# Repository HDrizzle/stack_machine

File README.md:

# Stack Machine Version 2

</img>

Photo of Version 1

## Changes from previous version

* The timing will be completely redone: A single normal clock signal, not the stupid "AB Alternating" I made up for the original.
* The PC will be incremented and a new instruction fetched during any non-flow-control instructions except when the GPRAM is used and the PC is in the same RAM chip (the RAM chips have 15 address lines each) as whatever is being accessed. The bus timing will also be very flexible and will be faster when possible but still slow when the memory is being accessed twice for example.
* Bus read/write addresses are both now 5 bits. The WRITE/MOVE instruction formats will remain the same and the extra bit (MSB to be exact) will be set based on duplicate opcodes for WRITE/MOVE that are otherwise interpreted the same. 1 extra WRITE opcode and 3 extra MOVE opcodes.
* The opcode decoder is actually 3 bits. There will be 4 bits used for extra MOVE/WRITE instructions (see above).
* Interrupts: There will be seperate interrupt GOTO latches that go to a dedicated interrupt handler function. That function should save the state of everything else (including the regular GOTO latches, which is why interrupt GOTO latches are seperate) onto the stack then do whatever depending on the interrupt code.
* GOTO latches can be written to the bus (see above). The goto decider doesn't need to be because it's simple to get its value from an IF-ELSE.
* The control unit will be able to fetch instructions from the GPRAM: Program addresses starting at 2^15 (32,768, halfway through the old flash memory space) will load 2 consecutive bytes (an instruction is 2 bytes) from the GPRAM. The GPRAM address of the first byte (lower byte of the instruction) will be determined by: `(prog_addr - 32,768) * 2`. Since that will only happen at or above 32,768 then the MSB will not be used in the math and will be used to determine whether to read from flash or GPRAM.
* Flash program space is selectable: The flash chips have 17 address lines, while 15 are used (see above about half the program address space being mapped to the GPRAM). This means that the top 2 lines can be connected to jumpers to select between 4 different programs.
* Flash program can be written to from the bus: The programming interface takes 8 data inputs + power and GND. The old interface to plug an Aduino in to program it will still be there of course but it can be selected by a jumper to be either the external pins (to Arduino) or from the bus.
* The stack is 32k instead of 64k so only one memory chip is used, although 32k is still incredibly excessive.

### GPRAM Parallelization

The RAM chips have 15 address lines each so there will be two of them (Lower and Upper Domains). This means that they can be used seperately at the same time, for example fetching the new instruction (If the PC is in the RAM) and also doing GPRAM read/write, as long as these operations are using seperate domains.
Memory users will use either (or both) of the lower or upper RAM domains:

* Program: PC and data read into instruction registers A & B
* Heap R/W: Exactly the same as the original

# Program instructions

Each instruction will be 16 bits and interpreted by the control unit. The first 3 bits (0 - 3) of the instruction will address the below list of operations. The rest of the instruction (bits 4 - 15) may be ignored or used for different things depending on the specific operation.

Here's the current list of the operation codes (opcodes):

0. `MOVE` - Bus usage - The rest of the instruction will be interpreted as follows: bits 8 - 11 address the device which will set the state of the bus (TX) and bits 12 - 15 will address the device to read from it (RX). Bits 4 - 7 are sent to the ALU as it's opcode incase the data is comming from it.
1. `WRITE` - Writes instruction bits 4 - 11 to the bus. Bits 12 - 15 address the device to read from it.
2. `GOTO` - Saves the 2 execution pointer GOTO latches (each of them are 1 byte) to the program counter
3. `GOTO-IF` - Reads the LSB of the value in the goto decider latch and does a GOTO only if it is 1, otherwise does nothing
4. `HALT` - Stops the clock, usefull for debugging
5. `CALL` - Effectively the same as `GOTO` but also pushes the return address (current value of program counter) onto the call stack. Note: The return address can be copied as-is and does not need to be incremented because it will be incremented normally after each `RETURN` instruction when it is used. If bit 4 is 1 this means that this call is calling the interrupt handler using the Interrupt GOTO latches.
6. `RETURN` - The program counter will be set to the return address popped off the top of the call stack. If bit 4 is 1 this means that this return instruction is returning from the interrupt handler function and will allow interrupts again.
7. `CONFIG-INT` - Configure interrupt. Bit 4 enables or disables interrupts. Interrupts are disabled on startup.

The following are treated as either MOVE or WRITE by the sequencer and set the bus TX and RX MSBs. The original MOVE and WRITE have all MSBs = 0.

8. `MOVE` - MSBs TX=1, RX=0
9. `MOVE` - MSBs TX=0, RX=1
10. `MOVE` - MSBs TX=1, RX=1
11. `WRITE` - MSBs RX=1

# Bus

Up to 15 devices can read the bus and 16 write to it.
Devices that can read the bus (RX):

0. `NONE` - Nothing reads this so that bytes can be popped from the stack without them going anywhere.
1. `STACK-PUSH` - Stack controller (Push)
2. `ALU-A` - ALU latch A
3. `ALU-B` - ALU latch B
4. `GOTO-A` - Control unit - Program counter GOTO latch A (first byte)
5. `GOTO-B` - Control unit - Program counter GOTO latch B (second byte)
6. `GOTO-DECIDER` - Control unit - GOTO decider latch (For GOTO-IF)
7. `GPRAM` - GPRAM - Write
8. `GPRAM-INC-ADDR` - GPRAM - Write (++ address)
9. `GPRAM-ADDR-A` - GPRAM - Address bits 0 - 7
10. `GPRAM-ADDR-B` - GPRAM - Address bits 8 - 15
11. `GPIO-WRITE-A` - Writes to GPIO output pins 0 - 7
12. `OFFSET-WRITE` - Replaces value in stack at `ToS - offset`
13. `SET-STACK-OFFSET` - Sets the stack offset byte
14. `ALU-C-IN` - ALU latch for carry and borrow, only LSB is used. Make sure this is always zero when not being used otherwise additions will be wrong.
15. `GPIO-WRITE-B` - Writes to GPIO output pins 8 - 15
16. `INT-GOTO-A` - Interrupt GOTO A
17. `INT-GOTO-B` - Interrupt GOTO B
18. `VECTORS-A` - Vector graphics A input
19. `VECTORS-B` - Vector graphics B input
20. `VECTORS-C` - Vector graphics C input
21. `VECTORS-D` - Vector graphics D input
22. `INT-AND-MAIN-TIMER-ADDRESS` - Bits 0 - 1 address 1 of the 4 interrupt timers. Bit 2 will reset the addressed counter to 0.
23. `INT-TIMER-CONFIG-MAX` - Sets the start value of one of the interrupt timers
24. `INT-TIMER-CONFIG-TIMEBASE-AND-ENABLE` - Configures one of the interrupt timers, see `timer_board.md`
25. `FLASH` - Flash programming interface, same as the arduino connection
26. `RX-26` - Expansion RX 25

...

31. `RX-31` - Expansion RX 31

Devices that can write to the bus (TX):

0. `STACK-POP` - Stack controller (pop)
1. `OFFSET-READ` - Reads value from stack at `ToS - offset`, does not affect the ToS
2. `ALU` - ALU output
3. Control unit instruction bits 4 - 11, used for the `WRITE` instruction
4. `GPRAM` - GPRAM - Read
5. `GPRAM-INC-ADDR` - GPRAM - Read (++ address)
6. `GPRAM-ADDR-A` - GPRAM - Address bits 0 - 7
7. `GPRAM-ADDR-B` - GPRAM - Address bits 8 - 15
8. `GPIO-READ-A` - Reads GPIO input pins 0 - 7
9. `MAIN-TIMER` - 8 bits of the main timer, addressed by `INT-AND-MAIN-TIMER-ADDRESS`
10. `INT-TIMER` - Current value of 1 of the 4 interrupt timers, addressed by `INT-AND-MAIN-TIMER-ADDRESS`
11. `GPIO-READ-B` - Reads GPIO input pins 8 - 15
12. `INT-CODE` - Most recent interrupt code, will be cleared upon read
13. `INT-COUNT` - Number of interrupts in queue, will overflow past 255
14. `GET-STACK-OFFSET` - Retrieves stack offset, needed to save state during interrupt
15. `GET-GOTO-A` - Read GOTO Latch A
16. `GET-GOTO-B` - Read GOTO Latch B
17. `TX-17` - Expansion TX 17

...

31. `TX-31` - Expansion TX 31

# The Stack

The stack will simply be a piece of memory seperate from the pGPRAM and managed by hardware, its has 32k x 8-bit words.

There will be two ways to access the stack:

1. Push and Pop
2. Using the current ToS pointer - stack offset (`OFFSET-WRITE` and `OFFSET-READ`) (does not change ToS). The stack offset will be a 1-byte number set from the bus (`SET-STACK-OFFSET`) and will not affect pushes and pops.

# ALU

The ALU uses 2 8-bit latches for input and has 1 output. The specific operation it does is controlled by 4 bits (2^4 = 16 operations). All operations that result in a boolean output all `0`s except for the result which is the LSB.

0. `ADD` - Add
1. `ADD-C` - Addition carry output (just the LSB will be set), this can be written directly into `ALU-C-IN`
2. `NOT` - Bitwise NOT (latch A)
3. `OR` - Bitwise OR
4. `AND` - Bitwise AND
5. `XNOR` - Bitwise XNOR, whether each pair of bits are equal
6. `SHIFT` - Bitshifts A left by the first 3 bits of B, bits that go off the end DO wrap around.
7. `EQ` - Whether bytes are equal
8. `A` - Contents of A latch
9. `B` - Contents of B latch
10. `EXT-10` - Extension (not implemented)
11. `EXT-11` - Extension (not implemented)
12. `EXT-12` - Extension (not implemented)
13. `EXT-13` - Extension (not implemented)
14. `EXT-14` - Extension (not implemented)
15. `EXT-15` - Extension (not implemented)

# Flow Control

There are four instructions for flow control: `GOTO`, `GOTO-IF`, `CALL`, and `RETURN`.

## GOTO and GOTO-IF

A `GOTO` instruction is used to jump to anywhere in the program. it uses the two 8-bit latches (`GOTO-A` and `GOTO-B`) to set the 16-bit program counter. Due to how the hardware is set up, the PC will be incremented after each goto instruction. This means that the previous address to where the execution should jump to must be used.

`GOTO-IF` is a conditional goto which will do what is described above only if the bit set by `GOTO-DECIDER` from the LSB of the bus is 1, otherwise it does nothing. This is the only instruction that allows the computer to "branch" or "make decisions".

There are macros, `@goto(anchor_name)` and `@goto_if(anchor_name)` that make GOTOs a lot easier.

## Functions and the call stack

Functions in the machine code are defined by `CALL` and `RETURN` instructions. To call a function, make sure the correct pointer to the beginning of the function is stored in the control unit goto A and B latches. Then use the `CALL` instruction which is basically a GOTO but will first put the current program counter value onto the call stack as the return address. The return instruction pops a return address off of the call stack and continues execution.

There is a macro in the assembly language, `@call(function_name)` that makes calling a lot easier.

The call stack is a seperate stack memory containing 256 (1 byte address size) 16-bit words. Each word will be a return address - where to set the program counter during a `RETURN` instruction.

# I/O

There are 16 input and 16 seperate output pins accessible with the `GPIO-READ-A`, `-B` and `GPIO-WRITE-A`, `-B` bus sources/destinations.

## Writing to the display

The display has 32 x 32 LEDs, any given row of 8 pixels are written all at once with one byte. These rows of 8 are addressed by a 7-bit number starting at the top-left and going across for 4 per row (32 / 8 = 4) for each of the 32 rows of the display. The display currently is attached to the gpio-write a and b outputs with gpio-write-a being the address (MSB is ignored) and gpio-write-b being the data. The signal to write the address/data to the display's memory is sent by the hardware when gpio-write-b is written to, meaning the address should be written first and then the data.

# General purpose static-RAM (GPRAM)

This piece of memory does not have any hardware protection like the stack and can be writen to and read from at any location. It will have a 16-bit address by 8-bit word size (65,536 bytes) just like the stack.

Its address can be optionally incremented upon reads/writes and can be directly set from the bus (`GPRAM-ADDR-A` and `GPRAM-ADDR-B`). For the instructions where the address is incremented, that will happen after the read/write.

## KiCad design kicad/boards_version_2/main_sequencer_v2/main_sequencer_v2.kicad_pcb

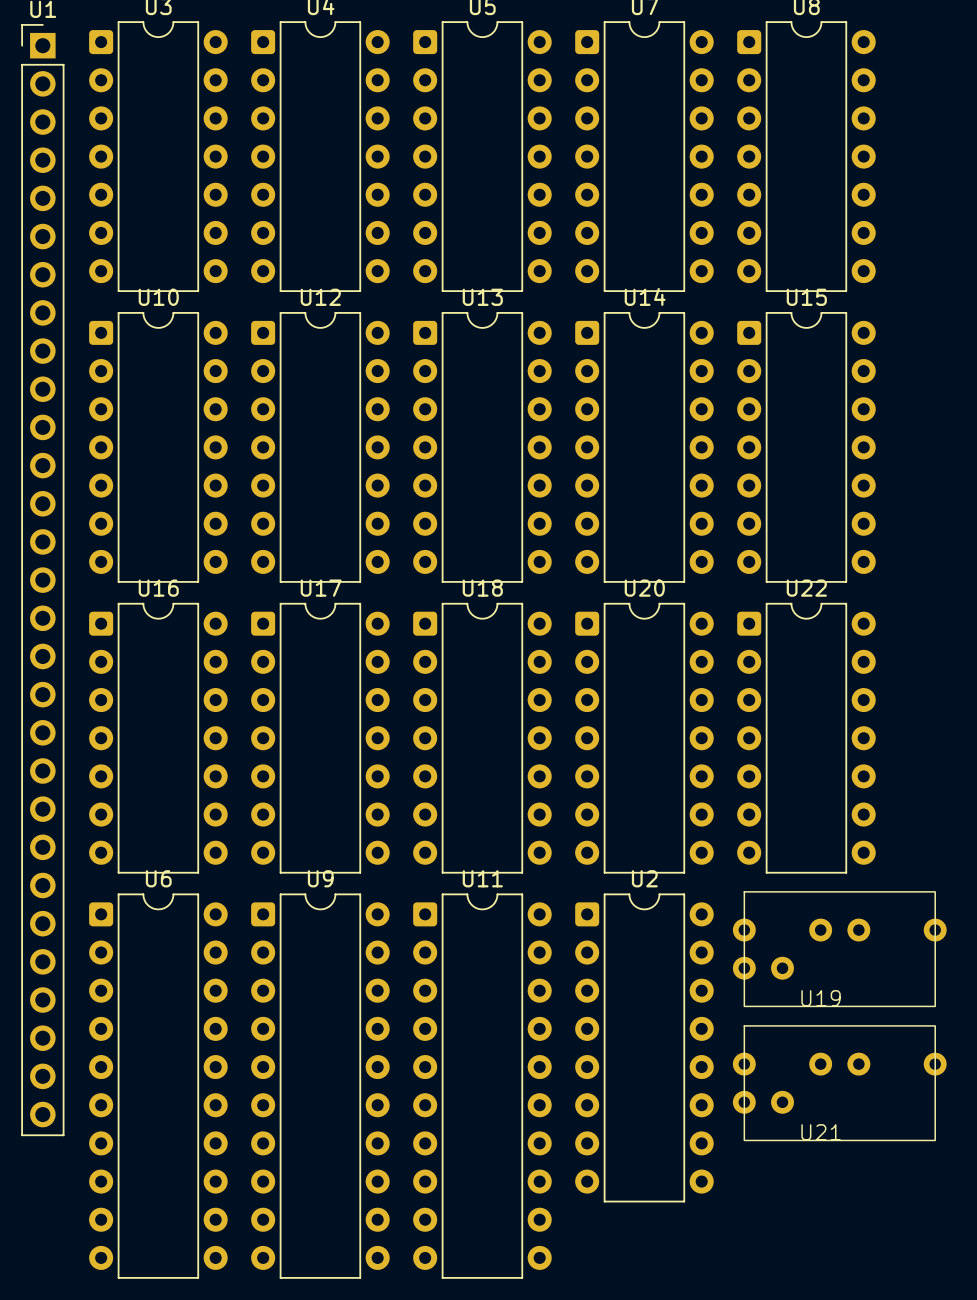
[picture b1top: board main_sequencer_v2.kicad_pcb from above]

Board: 2 copper layers, 22 parts (0 on the bottom side), 80 nets, no tracks yet.

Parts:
U1: PinHeader_1x29_P2.54mm_Vertical
U2: DIP-16_W7.62mm
U3, U4, U5, U7, U8, U10, U12, U13, U14, U15, U16, U17, U18, U20, U22: DIP-14_W7.62mm
U6, U9, U11: DIP-20_W7.62mm
U19, U21: jumper

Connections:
unnamed: U1.13 (Bus_move), U8.4 (Q1), U8.13 (3B)
unnamed: U1.2 (Bus_move_done), U16.4 (A2)
unnamed: U1.4 (CLK), U3.1 (I0), U9.11 (CLK)
unnamed: U1.5 (Enable), U4.1 (1A), U18.13 (I5)
unnamed: U1.3 (GOTO_Decider), U10.1 (0A)
unnamed: U1.16 (GOTO_latches_OE), U15.3 (1Q)
unnamed: U1.15 (INT-GOTO_latches_OE), U15.6 (2Q)
unnamed: U1.21 (Instruction++), U3.12 (O5)
unnamed: U1.9 (Instruction_bit_4), U3.5 (I2), U7.5 (0D), U13.2 (1B), U13.4 (2A), U13.10 (4A)
unnamed: U1.6 (Opcode_(3-bit)_0), U2.1 (A0)
unnamed: U1.7 (Opcode_(3-bit)_1), U2.2 (A1)
unnamed: U1.8 (Opcode_(3-bit)_2), U2.3 (A2)
unnamed: U1.17 (Post-adder_latch_OE), U5.4 (Q1)
unnamed: U1.19 (Pre-adder_latch_CLK), U9.4 (D2), U17.1 (OA)
unnamed: U1.11 (Start_-edge), U10.9 (2B)
unnamed: U2.6 (E1), U4.3 (1Q), U4.13 (3A)
unnamed: U2.4 (E2#), U2.5 (E3#), U2.8 (GND)
unnamed: U2.15 (Y0), U8.5 (1A)
unnamed: U2.14 (Y1), U8.6 (1B)
unnamed: U2.12 (Y3), U8.9 (2B)
unnamed: U2.11 (Y4), U6.5 (D3), U8.1 (0A)
unnamed: U2.10 (Y5), U6.2 (D0)
unnamed: U2.9 (Y6), U6.9 (D7)
unnamed: U3.4 (O1), U4.12 (3B)
unnamed: U4.11 (3Q), U6.8 (D6)
unnamed: U5.1 (0A), U9.17 (Q2)
unnamed: U6.18 (Q1), U9.3 (D1)
unnamed: U7.4 (0RESET), U7.6 (0SET), U7.7 (GND)
unnamed: U8.3 (Q0), U8.12 (3A)
unnamed: U2.13 (Y2), U8.8 (2A), U10.2 (0B)
unnamed: U6.3 (D1), U9.19 (Q0), U10.5 (1A)
unnamed: U6.19 (Q0), U7.3 (0CLK), U9.2 (D0), U10.6 (1B), U13.1 (1A)
unnamed: U6.15 (Q4), U10.8 (2A)
unnamed: U6.4 (D2), U9.18 (Q1), U10.12 (3A), U14.13 (3A)
unnamed: U10.13 (3B), U14.6 (2Q)
unnamed: U3.11 (I4), U10.3 (Q0), U14.4 (2A)
unnamed: U10.4 (Q1), U16.10 (B1)
unnamed: U10.10 (Q2), U17.3 (A1)
unnamed: U10.11 (Q3), U15.2 (1B), U15.5 (2B)
unnamed: U3.14 (V+), U8.14 (V+), U10.14 (V+), U13.14 (V+), U16.14 (V+)
unnamed: U3.2 (O0), U6.11 (CLK), U11.11 (CLK)
unnamed: U2.7 (Y7), U8.2 (0B), U11.2 (D0)
unnamed: U6.1 (OE#), U6.10 (GND), U9.1 (OE#), U9.10 (GND), U11.10 (GND)
unnamed: U11.19 (Q0), U13.9 (4B), U13.12 (3B), U16.5 (A3)
unnamed: U6.20 (V+), U9.20 (V+), U11.20 (V+)
unnamed: U12.1 (0A), U18.6 (O2), U19.1 (IN)
unnamed: U12.2 (0B), U13.3 (1Q)
unnamed: U12.5 (1A), U18.4 (O1)
unnamed: U5.10 (Q2), U12.6 (1B)
unnamed: U12.8 (2A), U18.10 (O4), U21.1 (IN)
unnamed: U12.9 (2B), U13.8 (4Q)
unnamed: U12.12 (3A), U18.8 (03)
unnamed: U5.11 (Q3), U12.13 (3B)
unnamed: U12.3 (Q0), U18.3 (I1)
unnamed: U12.4 (Q1), U18.5 (I2)
unnamed: U12.10 (Q2), U18.9 (I3)
unnamed: U12.11 (Q3), U18.11 (I4)
unnamed: U3.13 (I5), U5.8 (2A), U13.6 (2Q)
unnamed: U3.6 (O2), U13.13 (3A)
unnamed: U5.13 (3B), U13.11 (3Q)
unnamed: U3.10 (O4), U14.1 (1A)
unnamed: U6.6 (D4), U8.10 (Q2), U14.2 (1B), U14.5 (2B)
unnamed: U14.3 (1Q), U16.9 (B0)
unnamed: U7.1 (0Q), U14.12 (3B)
unnamed: U3.9 (I3), U14.11 (3Q), U15.4 (2A)
unnamed: U14.9 (4B), U21.3 (OUT)
unnamed: U3.8 (03), U15.1 (1A)
unnamed: U15.13 (3A), U16.1 (OA), U18.1 (I0)
unnamed: U15.12 (3B), U18.2 (O0)
unnamed: U6.13 (Q6), U16.2 (A0)
unnamed: U6.16 (Q3), U16.3 (A1)
unnamed: U3.3 (I1), U6.7 (D5), U8.11 (Q3), U16.11 (B2)
unnamed: U5.3 (Q0), U16.12 (B3)
unnamed: U5.5 (1A), U16.13 (OB)
unnamed: U6.14 (Q5), U17.2 (A0)
unnamed: U6.17 (Q2), U17.4 (A2)
unnamed: U6.12 (Q7), U17.5 (A3)
unnamed: U17.7 (GND), U17.12 (B3)
unnamed: U5.9 (2B), U5.12 (3A), U18.12 (O5)
unnamed: U19.2 (GND), U21.2 (GND)

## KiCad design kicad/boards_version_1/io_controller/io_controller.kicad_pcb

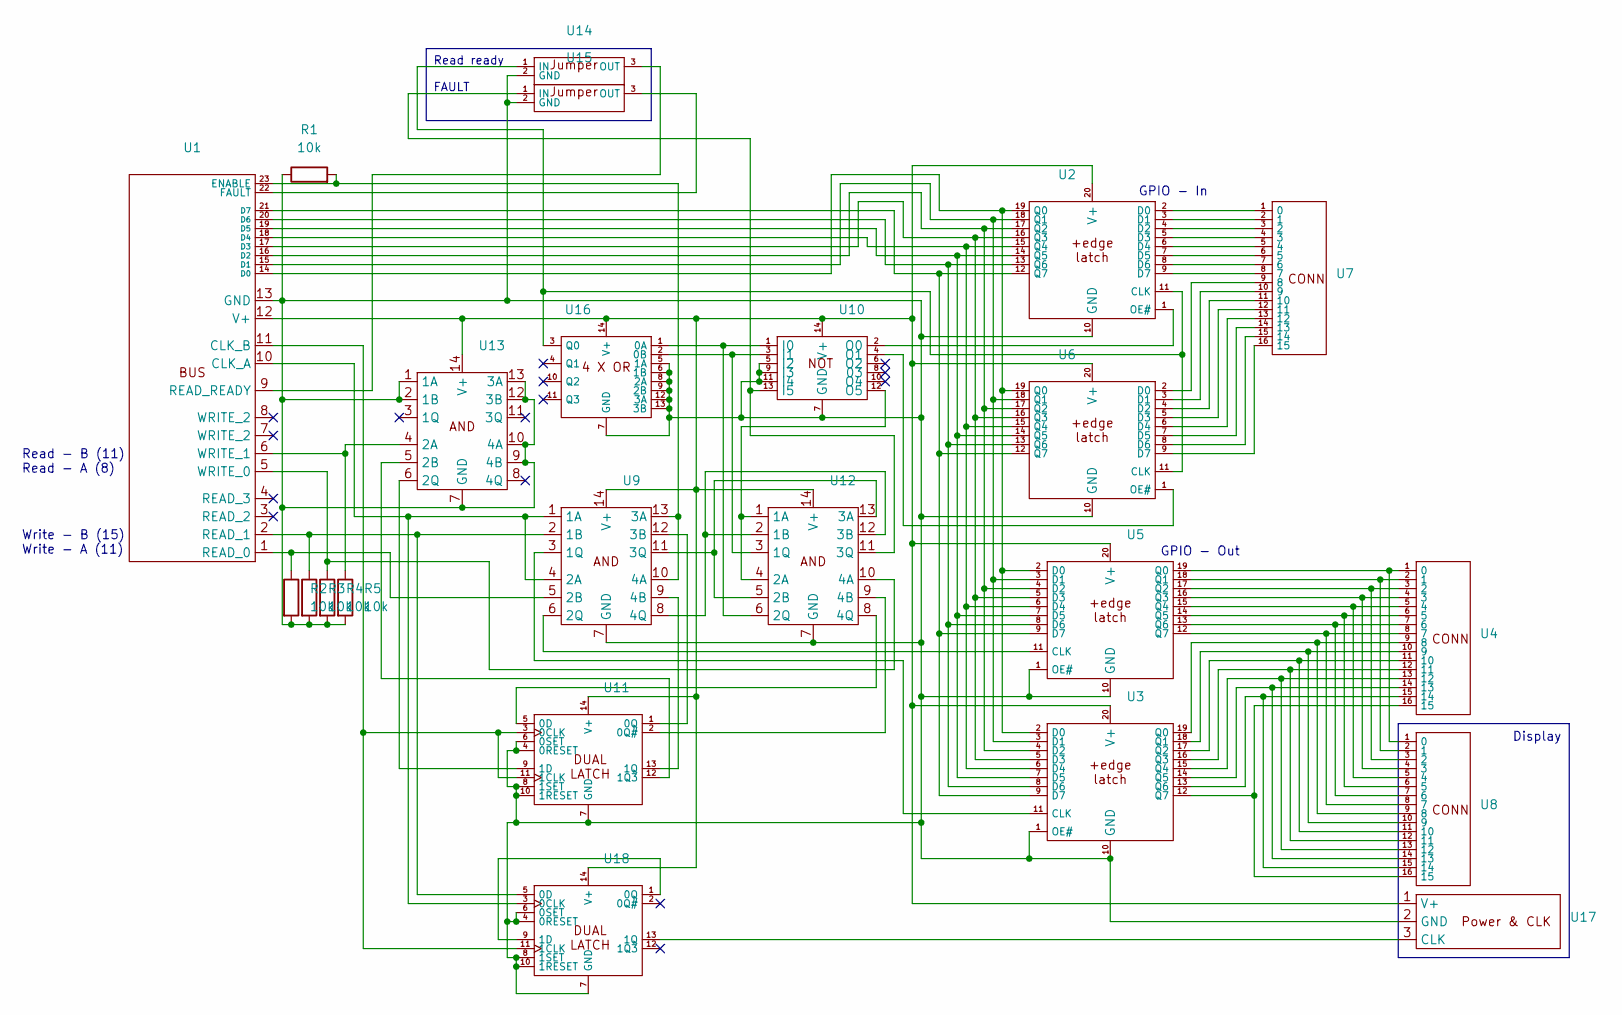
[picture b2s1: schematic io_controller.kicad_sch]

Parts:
R1, R2, R3, R4, R5: 10k; 0.4_pitch_resistor
U1: PinHeader_1x23_P2.54mm_Vertical
U2, U3, U5, U6: DIP-20_W7.62mm
U4, U7, U8: PinHeader_1x16_P2.54mm_Vertical
U9, U10, U11, U12, U13, U16, U18: DIP-14_W7.62mm
U14, U15: jumper
U17: PinHeader_1x03_P2.54mm_Vertical

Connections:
unnamed: U1.10 (CLK_A), U9.1 (1A), U9.4 (2A), U18.3 (0CLK)
unnamed: U1.11 (CLK_B), U11.3 (0CLK), U11.11 (1CLK), U18.11 (1CLK)
unnamed: U1.14 (D0), U2.19 (Q0), U3.2 (D0), U5.2 (D0), U6.19 (Q0)
unnamed: U1.15 (D1), U2.18 (Q1), U3.3 (D1), U5.3 (D1), U6.18 (Q1)
unnamed: U1.16 (D2), U2.17 (Q2), U3.4 (D2), U5.4 (D2), U6.17 (Q2)
unnamed: U1.17 (D3), U2.16 (Q3), U3.5 (D3), U5.5 (D3), U6.16 (Q3)
unnamed: U1.18 (D4), U2.15 (Q4), U3.6 (D4), U5.6 (D4), U6.15 (Q4)
unnamed: U1.19 (D5), U2.14 (Q5), U3.7 (D5), U5.7 (D5), U6.14 (Q5)
unnamed: U1.20 (D6), U2.13 (Q6), U3.8 (D6), U5.8 (D6), U6.13 (Q6)
unnamed: U1.21 (D7), U2.12 (Q7), U3.9 (D7), U5.9 (D7), U6.12 (Q7)
unnamed: R1.2, U1.23 (ENABLE), U9.10 (4A), U9.13 (3A)
unnamed: U1.22 (FAULT), U15.3 (OUT)
unnamed: R1.1, R2.2, R3.2, R4.2, R5.2, U1.13 (GND), U2.10 (GND), U3.1 (OE#), U3.10 (GND), U5.1 (OE#), U5.10 (GND), U6.10 (GND), U9.7 (GND), U10.5 (I2), U10.7 (GND), U10.9 (I3), U10.11 (I4), U11.4 (0RESET), U11.6 (0SET), U11.7 (GND), U11.8 (1SET), U11.10 (1RESET), U12.7 (GND), U13.1 (1A), U13.2 (1B), U13.7 (GND), U13.9 (4B), U13.10 (4A), U13.12 (3B), U13.13 (3A), U14.2 (GND), U15.2 (GND), U16.5 (1A), U16.6 (1B), U16.7 (GND), U16.8 (2A), U16.9 (2B), U16.12 (3A), U16.13 (3B), U17.2 (GND), U18.4 (0RESET), U18.6 (0SET), U18.7 (GND), U18.8 (1SET), U18.10 (1RESET)
unnamed: R2.1, U1.1 (READ_0), U9.5 (2B)
unnamed: R3.1, U1.2 (READ_1), U9.2 (1B), U18.5 (0D)
unnamed: U1.9 (READ_READY), U14.3 (OUT)
unnamed: U1.12 (V+), U2.20 (V+), U3.20 (V+), U5.20 (V+), U6.20 (V+), U9.14 (V+), U10.14 (V+), U11.14 (V+), U12.14 (V+), U13.14 (V+), U16.14 (V+), U17.1 (V+), U18.14 (V+)
unnamed: R4.1, U1.5 (WRITE_0), U12.10 (4A)
unnamed: R5.1, U1.6 (WRITE_1), U13.4 (2A)
unnamed: U2.2 (D0), U7.1 (0)
unnamed: U2.3 (D1), U7.2 (1)
unnamed: U2.4 (D2), U7.3 (2)
unnamed: U2.5 (D3), U7.4 (3)
unnamed: U2.6 (D4), U7.5 (4)
unnamed: U2.7 (D5), U7.6 (5)
unnamed: U2.8 (D6), U7.7 (6)
unnamed: U2.9 (D7), U7.8 (7)
unnamed: U3.11 (CLK), U9.3 (1Q)
unnamed: U3.19 (Q0), U4.9 (8), U8.9 (8)
unnamed: U3.18 (Q1), U4.10 (9), U8.10 (9)
unnamed: U3.17 (Q2), U4.11 (10), U8.11 (10)
unnamed: U3.16 (Q3), U4.12 (11), U8.12 (11)
unnamed: U3.15 (Q4), U4.13 (12), U8.13 (12)
unnamed: U3.14 (Q5), U4.14 (13), U8.14 (13)
unnamed: U3.13 (Q6), U4.15 (14), U8.15 (14)
unnamed: U3.12 (Q7), U4.16 (15), U8.16 (15)
unnamed: U4.1 (0), U5.19 (Q0), U8.1 (0)
unnamed: U4.2 (1), U5.18 (Q1), U8.2 (1)
unnamed: U4.3 (2), U5.17 (Q2), U8.3 (2)
unnamed: U4.4 (3), U5.16 (Q3), U8.4 (3)
unnamed: U4.5 (4), U5.15 (Q4), U8.5 (4)
unnamed: U4.6 (5), U5.14 (Q5), U8.6 (5)
unnamed: U4.7 (6), U5.13 (Q6), U8.7 (6)
unnamed: U4.8 (7), U5.12 (Q7), U8.8 (7)
unnamed: U5.11 (CLK), U9.6 (2Q)
unnamed: U6.2 (D0), U7.9 (8)
unnamed: U6.3 (D1), U7.10 (9)
unnamed: U6.4 (D2), U7.11 (10)
unnamed: U6.5 (D3), U7.12 (11)
unnamed: U6.6 (D4), U7.13 (12)
unnamed: U6.7 (D5), U7.14 (13)
unnamed: U6.8 (D6), U7.15 (14)
unnamed: U6.9 (D7), U7.16 (15)
unnamed: U10.1 (I0), U12.6 (2Q), U16.1 (0A)
unnamed: U10.3 (I1), U12.3 (1Q), U16.2 (0B)
unnamed: U10.13 (I5), U12.11 (3Q), U15.1 (IN)
unnamed: U2.1 (OE#), U10.2 (O0)
unnamed: U6.1 (OE#), U10.4 (O1)
unnamed: U10.12 (O5), U12.1 (1A), U12.4 (2A)
unnamed: U11.5 (0D), U12.8 (4Q)
unnamed: U11.2 (0Q#), U12.9 (4B)
unnamed: U9.12 (3B), U11.1 (0Q)
unnamed: U11.9 (1D), U13.6 (2Q)
unnamed: U11.12 (1Q3), U13.5 (2B)
unnamed: U9.9 (4B), U11.13 (1Q)
unnamed: U9.8 (4Q), U12.2 (1B), U12.12 (3B)
unnamed: U9.11 (3Q), U12.5 (2B), U12.13 (3A)
unnamed: U2.11 (CLK), U6.11 (CLK), U14.1 (IN), U16.3 (Q0)
unnamed: U17.3 (CLK), U18.13 (1Q)
unnamed: U18.1 (0Q), U18.9 (1D)

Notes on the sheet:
Read ready FAULT
Display
Read - B (11) Read - A (8)
GPIO - Out
GPIO - In
Write - B (15) Write - A (11)

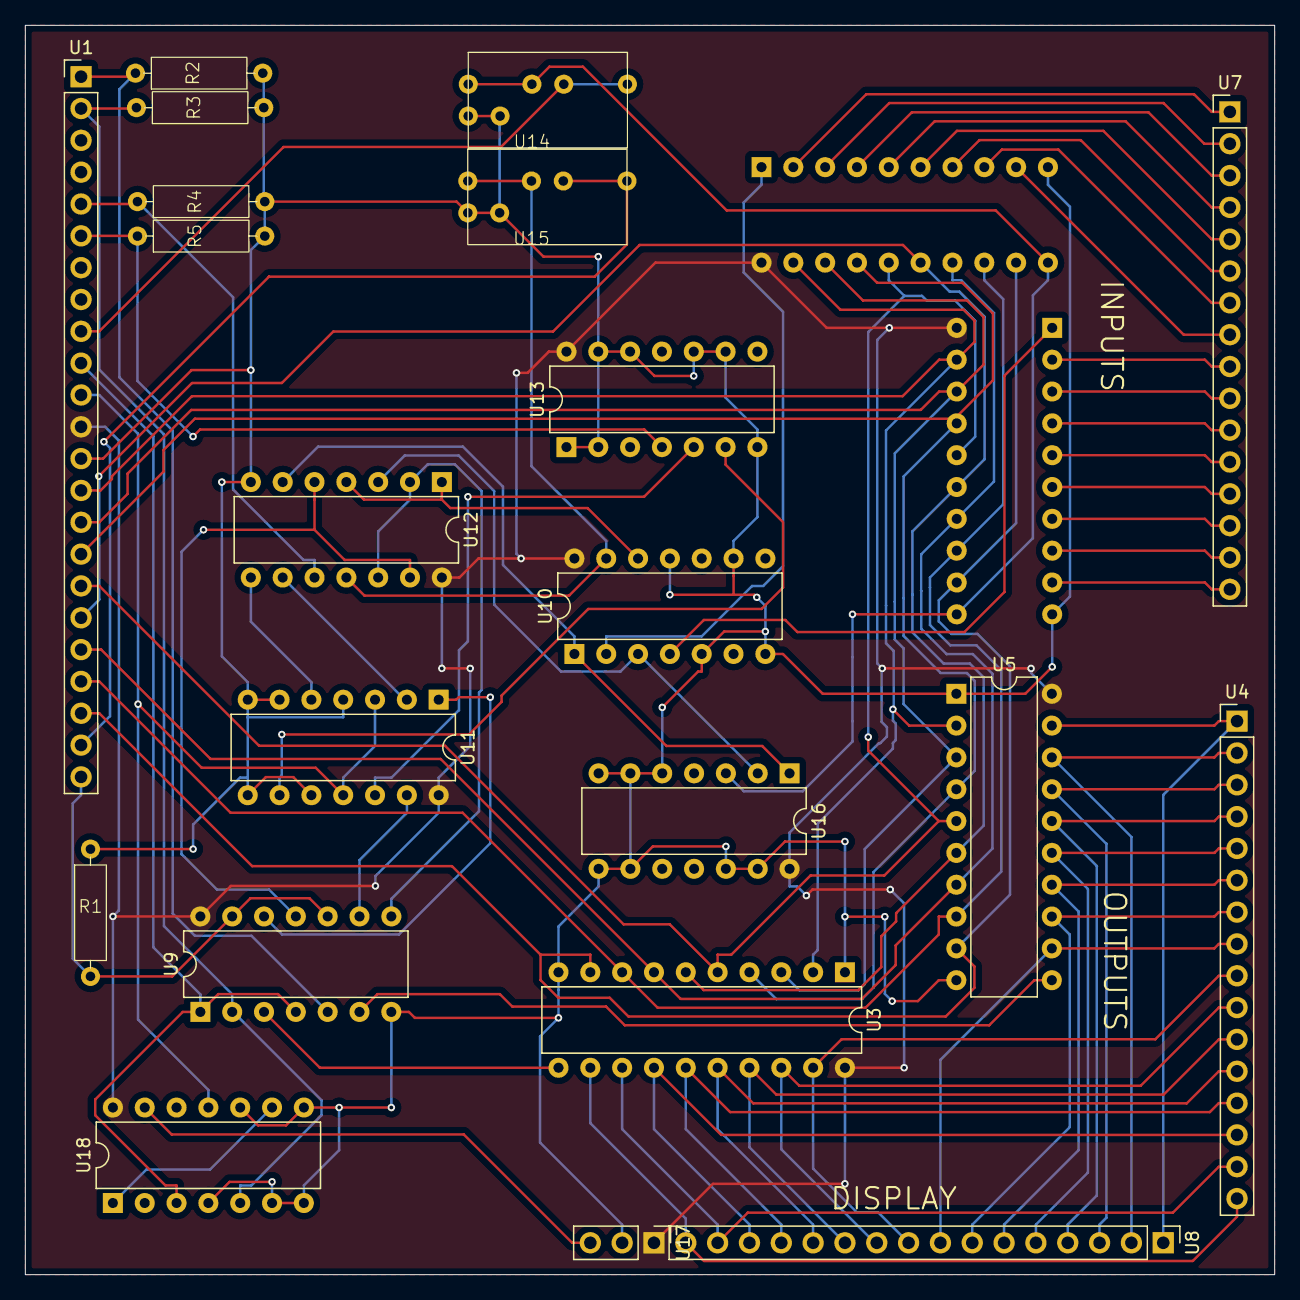
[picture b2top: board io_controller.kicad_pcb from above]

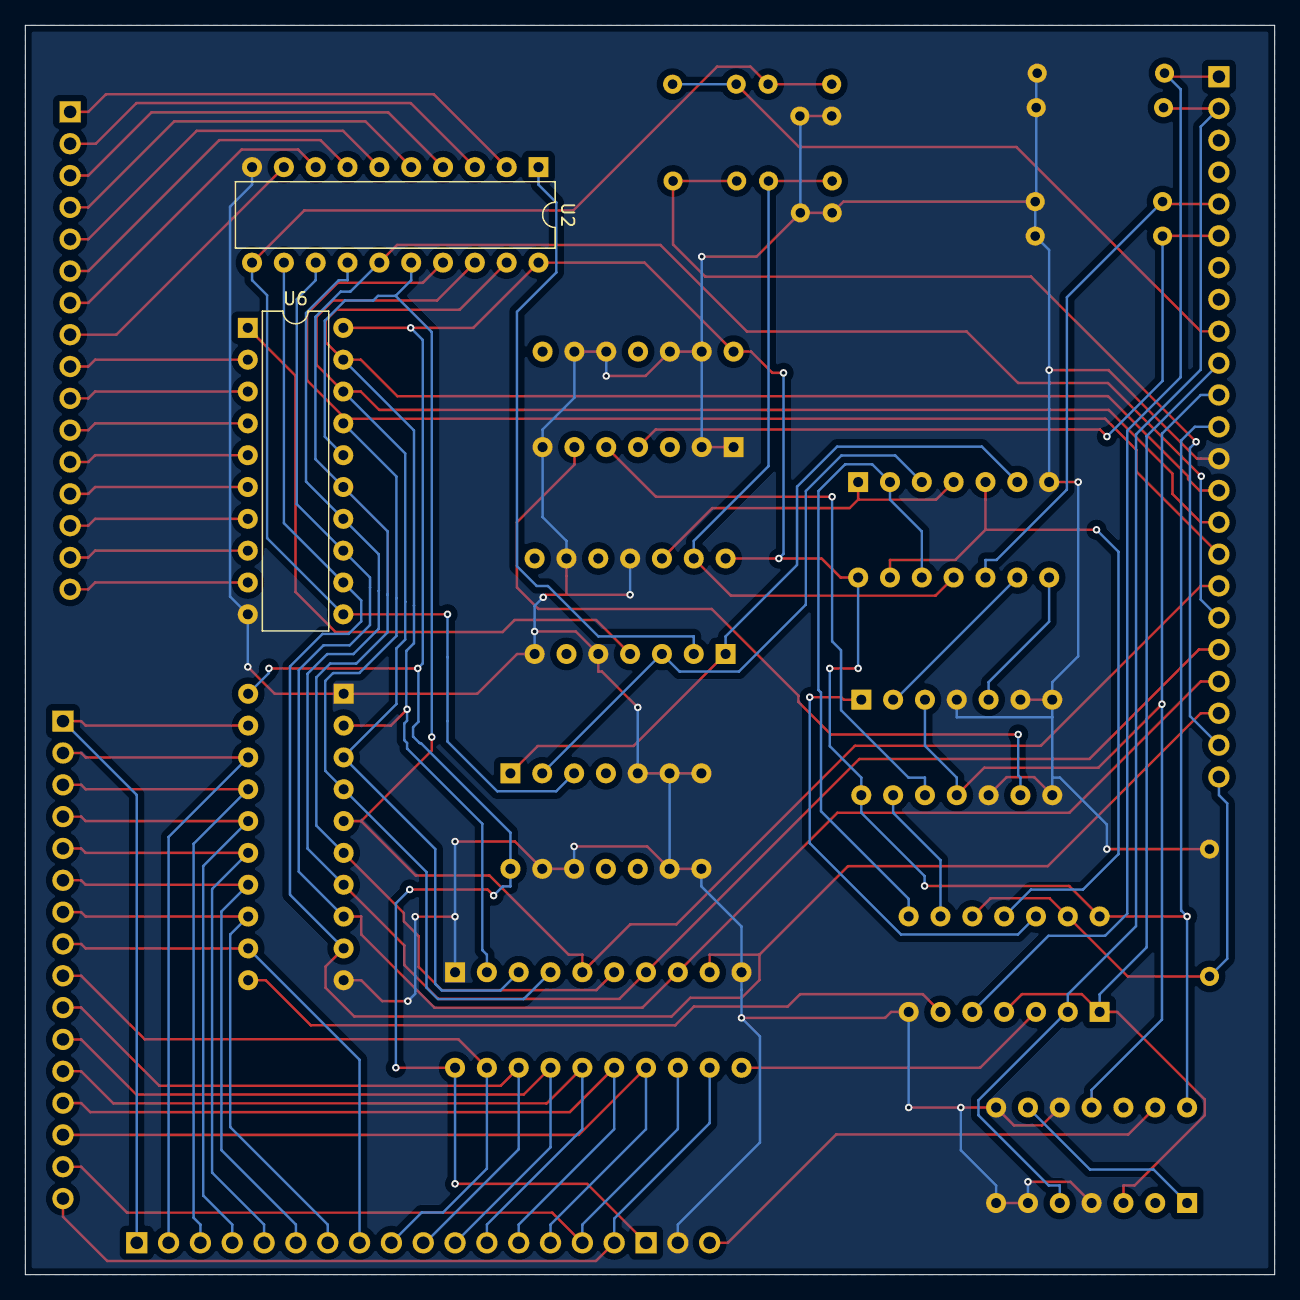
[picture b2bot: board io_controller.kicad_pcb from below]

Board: 2 copper layers, 99.7 x 99.7 mm, 23 parts (2 on the bottom side), 70 nets.

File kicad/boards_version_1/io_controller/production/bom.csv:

Designator,Footprint,Quantity,Value,LCSC Part #
"R1, R2, R3, R4, R5",0.4_pitch_resistor,5,10k,
U1,PinHeader_1x23_P2.54mm_Vertical,1,~,
"U10, U11, U12, U13, U16, U18, U9",DIP-14_W7.62mm,7,~,
"U14, U15",jumper,2,~,
U17,PinHeader_1x03_P2.54mm_Vertical,1,~,
"U2, U3, U5, U6",DIP-20_W7.62mm,4,~,
"U4, U7, U8",PinHeader_1x16_P2.54mm_Vertical,3,~,
